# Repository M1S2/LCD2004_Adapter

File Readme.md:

# LCD2004 Adapter

This is an adapter to connect the DZ2004A-V1.0 LCD (Geeetech Prusa i3 pro B display) to the BIGTREETECH SKR E3 DIP V1.1 main board (LCD port).
This adapter is necessary because:
- The wiring of the LCD connectors on the display and the main board are different. The LCD2004 adapter connects the correct traces to make the display work again.
- The encoder isn't used anymore. The LCD2004 adapter is adding 5 push buttons as replacement for the encoder. The principle is inspired by the Zonestar LCD. 

Limitations:
- The encoder is out of service. This isn't a big deal, because it wasn't used that often because Octoprint is used most of the time to control the printer. So the 5 button keypad seemed to be good enough. Refer to section "Using the encoder again" of this Readme for some links how the encoder can maybe be used again.

## Principle of the 5 button keypad
The LCD2004 adapter is using 5 buttons to control the printers functions. This is inspired by the Zonestar display. 
Depending on which button is pressed, a different voltage is generated at the ADC_KEYPAD pin. This pin is read by an ADC on the main board.
The "UP" button is located on the bottom side of the PCB. This is correct because up means scrolling up which is the button on the bottom.

**Caution:** The SKR E3 DIP main board (and many other 32-bit boards) are working on 3.3V logic. Most pins on the ARM Cortex M3 STM32F103RCT6 are 5V tolerant (you can connect 5V to them) **but the ADC pin isn't (don't connect 5V to it)**! The LCD2004_Adapter uses a 3.3V zener diode to produce the correct voltage.

## PCB
The schematic and PCB was created using EAGLE. It was designed to be manufactured using toner transfer method so all traces are as big as possible.

## Housing
Print the following parts:
- 1x Keys_Housing.stl
- 1x Key_Back.stl and Key_Back_Icon.stl in one part
- 1x Key_Enter.stl and Key_Enter_Icon.stl in one part
- 1x Key_Home.stl and Key_Home_Icon.stl in one part
- 2x Key_Up_Down.stl and Key_Up_Down_Icon.stl in one part

**Caution:** The back, enter and home buttons are each 2 mm shorter because 2mm longer buttons were used here. The up and down buttons have the "correct" length.

The following parts are needed additionally:
- 2x 12mm spacers
- 1x M3 screw 10mm & M3 nut
- 2x wood screws 10mm

## Cabling
A default 10-pin ribbon cable can be used to connect the adapter with the main board. 
The only thing that must be changed here is to extract pin 8 (ADC_KEYPAD) on the main board side of the cable and wire it to the Servo pin (PA1) on the SKR E3 DIP board.

Cable complete                                |  SKR E3 DIP side
:--------------------------------------------:|:-------------------------:
 |  

## Firmware adaptions
Make the following adaptions to the Marlin firmware (line numbers are refering to Marlin 2.0.8):
- <Marlin root>/Marlin/Configuration.h: 
  Uncomment the `#define ZONESTAR_LCD` (in line 2086)
- <Marlin root>/Marlin/src/pins/stm32f1/pins_BTT_SKR_E3_DIP.h:
  Comment the line 190: `#error "CAUTION! ZONESTAR_LCD requires wiring modifications. See 'pins_BTT_SKR_MINI_E3_common.h' for details. Comment out this line to continue."`

## More Images
More images can be found in the [Images](/Images/) folder.

## Using the encoder again
To use the encoder again instead of the 5 buttons, here are some inspirations. Because Octoprint is used most of the time, there wasn't spent much time on this.

https://electronics.stackexchange.com/questions/231803/rotary-encoder-to-2-buttons

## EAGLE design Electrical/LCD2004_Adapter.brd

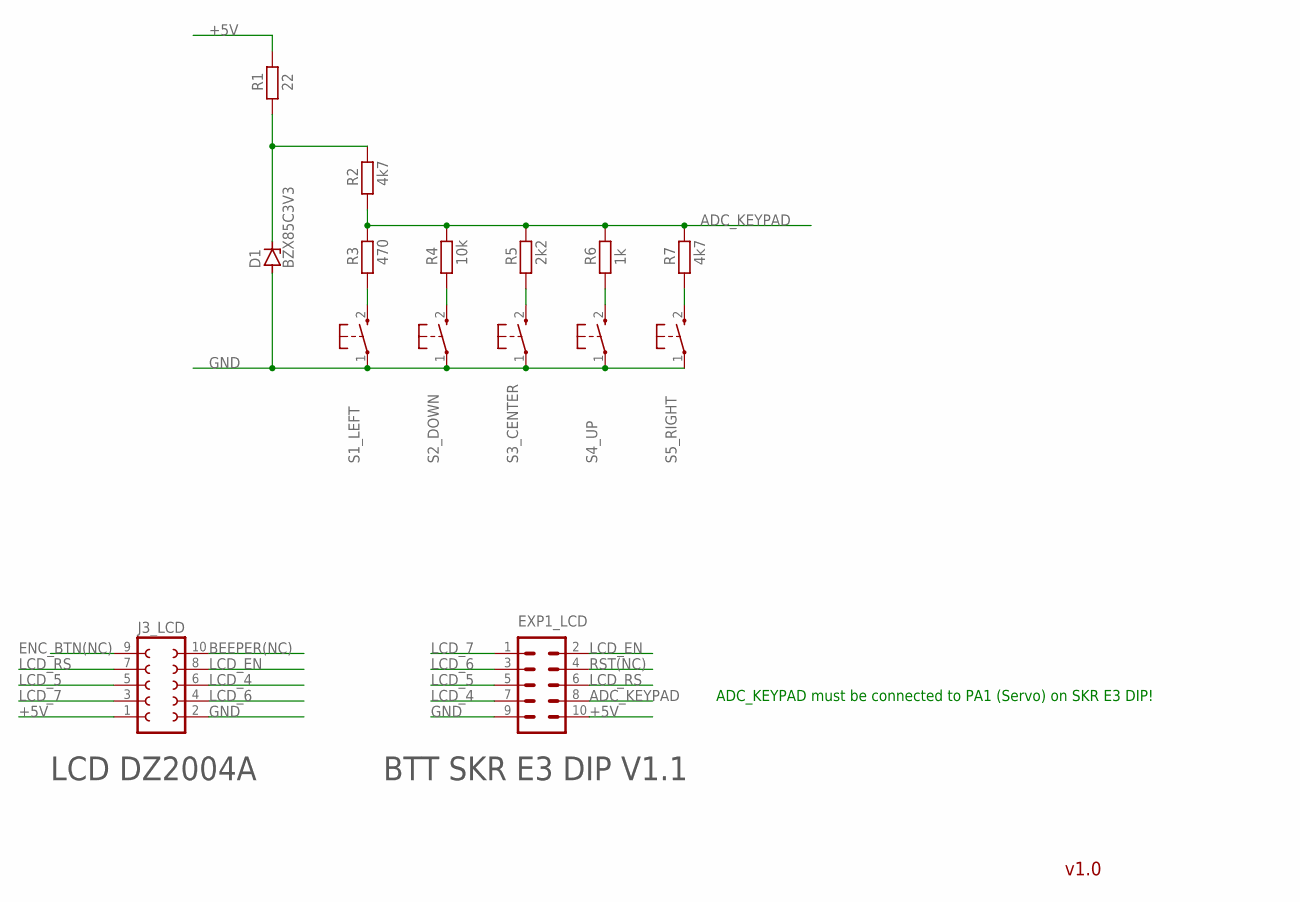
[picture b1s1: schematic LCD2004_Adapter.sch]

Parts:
D1: BZX85C3V3; DO41Z10
EXP1_LCD: ML10
J3_LCD: FE05-2
R1: 22; 0207/10
R2, R7: 4k7; 0207/10
R3: 470; 0207/10
R4: 10k; 0207/10
R5: 2k2; 0207/10
R6: 1k; 0207/10
S1_LEFT, S2_DOWN, S3_CENTER, S4_UP, S5_RIGHT: KURZHUBTASTER; B3F-10XX

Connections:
+5V: EXP1_LCD.10, J3_LCD.1, R1.2
ADC_KEYPAD: EXP1_LCD.8, R2.1, R3.2, R4.2, R5.2, R6.2, R7.2
BEEPER(NC): J3_LCD.10
ENC_BTN(NC): J3_LCD.9
GND: D1.A, EXP1_LCD.9, J3_LCD.2, S1_LEFT.1, S2_DOWN.1, S3_CENTER.1, S4_UP.1, S5_RIGHT.1
LCD_4: EXP1_LCD.7, J3_LCD.6
LCD_5: EXP1_LCD.5, J3_LCD.5
LCD_6: EXP1_LCD.3, J3_LCD.4
LCD_7: EXP1_LCD.1, J3_LCD.3
LCD_EN: EXP1_LCD.2, J3_LCD.8
LCD_RS: EXP1_LCD.6, J3_LCD.7
unnamed: D1.C, R1.1, R2.2
unnamed: R3.1, S1_LEFT.2 (S)
unnamed: R4.1, S2_DOWN.2 (S)
unnamed: R5.1, S3_CENTER.2 (S)
unnamed: R6.1, S4_UP.2 (S)
unnamed: R7.1, S5_RIGHT.2 (S)
RST(NC): EXP1_LCD.4

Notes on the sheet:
LCD DZ2004A
BTT SKR E3 DIP V1.1
ADC_KEYPAD must be connected to PA1 (Servo) on SKR E3 DIP!
v1.0

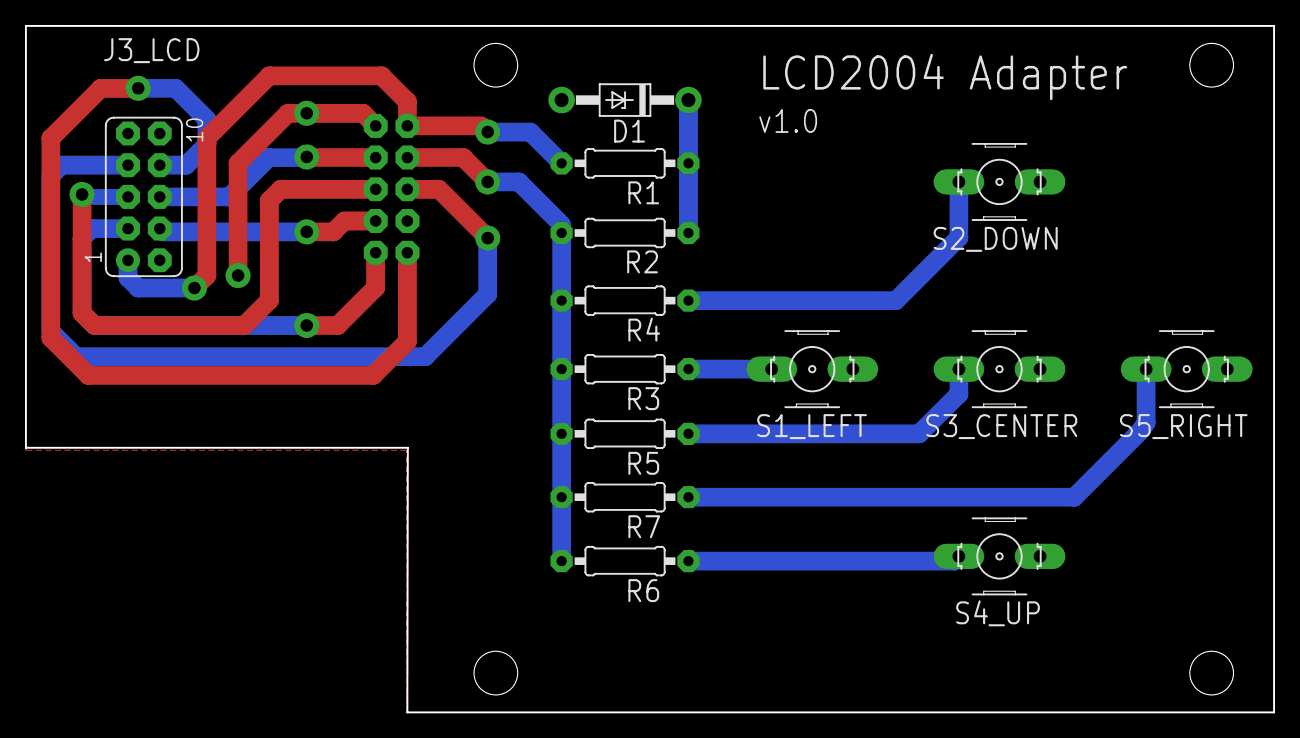
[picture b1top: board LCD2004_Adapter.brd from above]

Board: 2 copper layers, 100.0 x 55.0 mm, 15 parts (1 on the bottom side), 15 nets.

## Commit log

2021-04-30 Initial commit containing all electrical files
2021-05-03 Swapped Up and Down buttons on PCB (making equal to Zonestar LCD)
2021-05-03 Mechanical design added
2021-05-03 Readme updated
2021-05-03 Added license file
2021-05-03 Added Images and adapted Readme
2021-05-03 Small changes to Readme
